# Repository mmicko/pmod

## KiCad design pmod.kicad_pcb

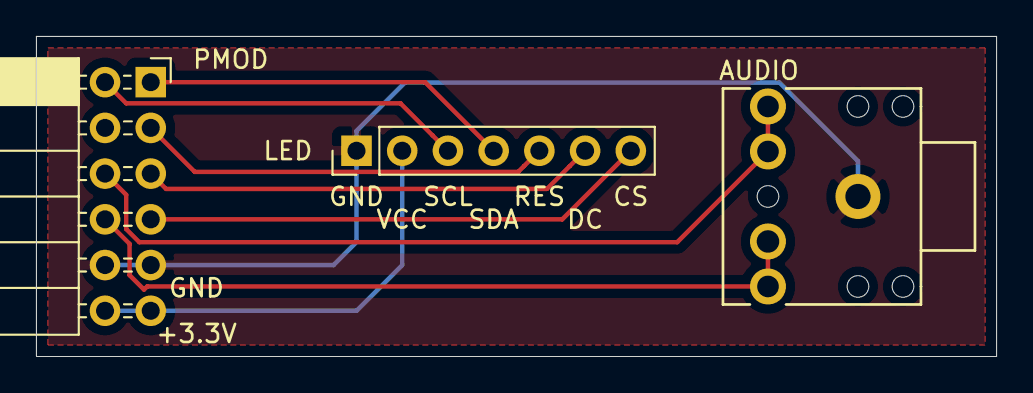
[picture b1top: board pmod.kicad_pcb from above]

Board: 2 copper layers, 53.3 x 17.8 mm, 3 parts (0 on the bottom side), 9 nets.

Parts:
AUDIO: AudioJack2_Ground; AUDIO_JACK_3.5mm
LED: Conn_01x07; PinHeader_1x07_P2.54mm_Vertical
PMOD: Conn_02x06_Odd_Even; PinSocket_2x06_P2.54mm_Horizontal

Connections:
+3V3: LED.2, PMOD.11, PMOD.12
AUDIO_L: AUDIO.S, PMOD.6
AUDIO_R: AUDIO.T, PMOD.8
CS: LED.7, PMOD.7
DC: LED.6, PMOD.5
GND: AUDIO.G, LED.1, PMOD.9, PMOD.10
RES: LED.5, PMOD.3
SCL: LED.3, PMOD.2
SDA: LED.4, PMOD.1

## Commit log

2020-02-23 Initial design
